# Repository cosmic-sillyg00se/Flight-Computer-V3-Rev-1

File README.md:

# Flight-Computer-V3-Rev-1
(04/2025) Slighty better than my last try, still a total mess tho (also didn't work at all)

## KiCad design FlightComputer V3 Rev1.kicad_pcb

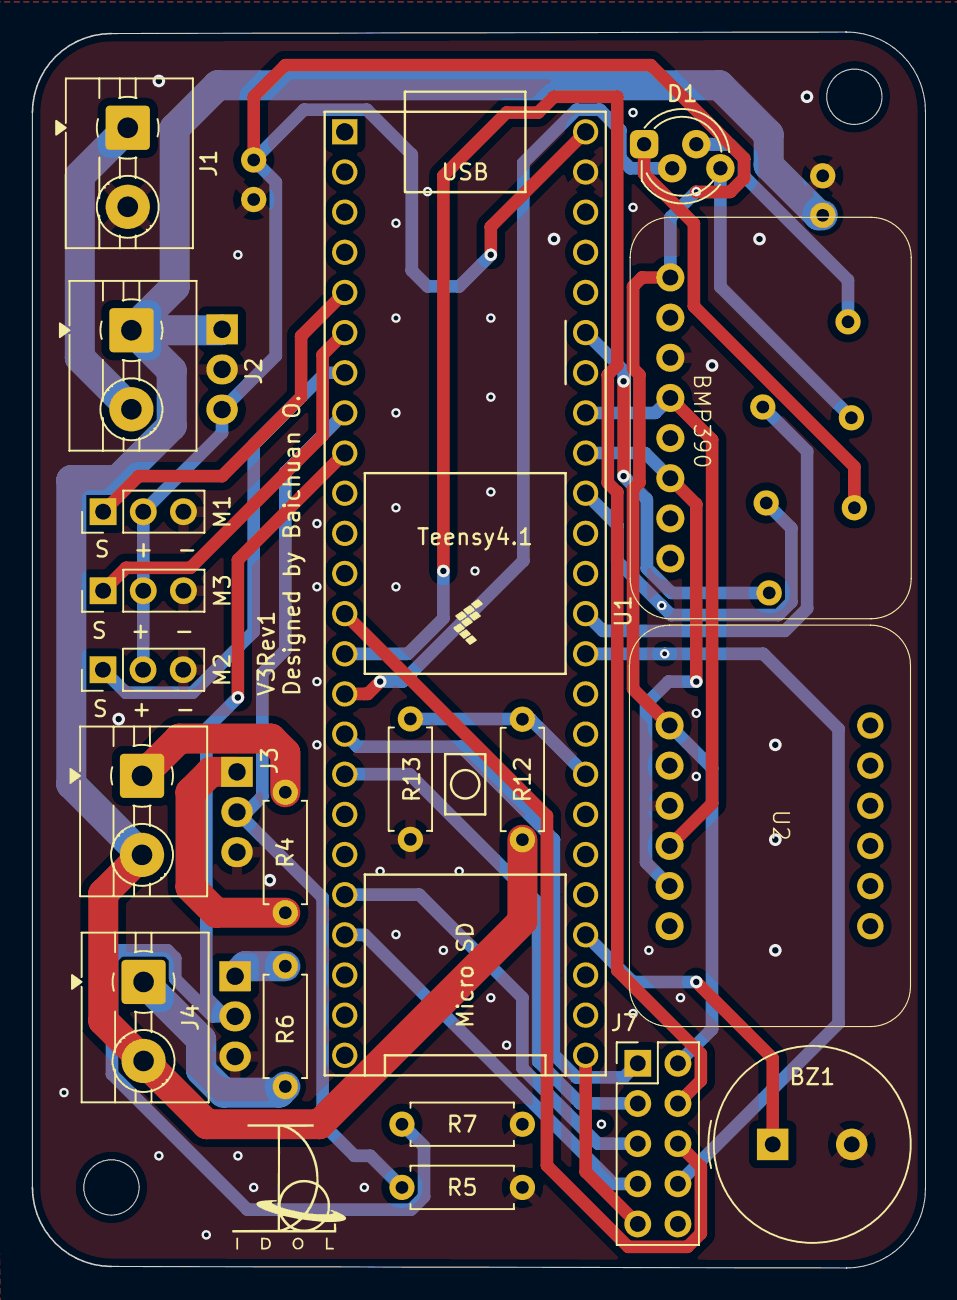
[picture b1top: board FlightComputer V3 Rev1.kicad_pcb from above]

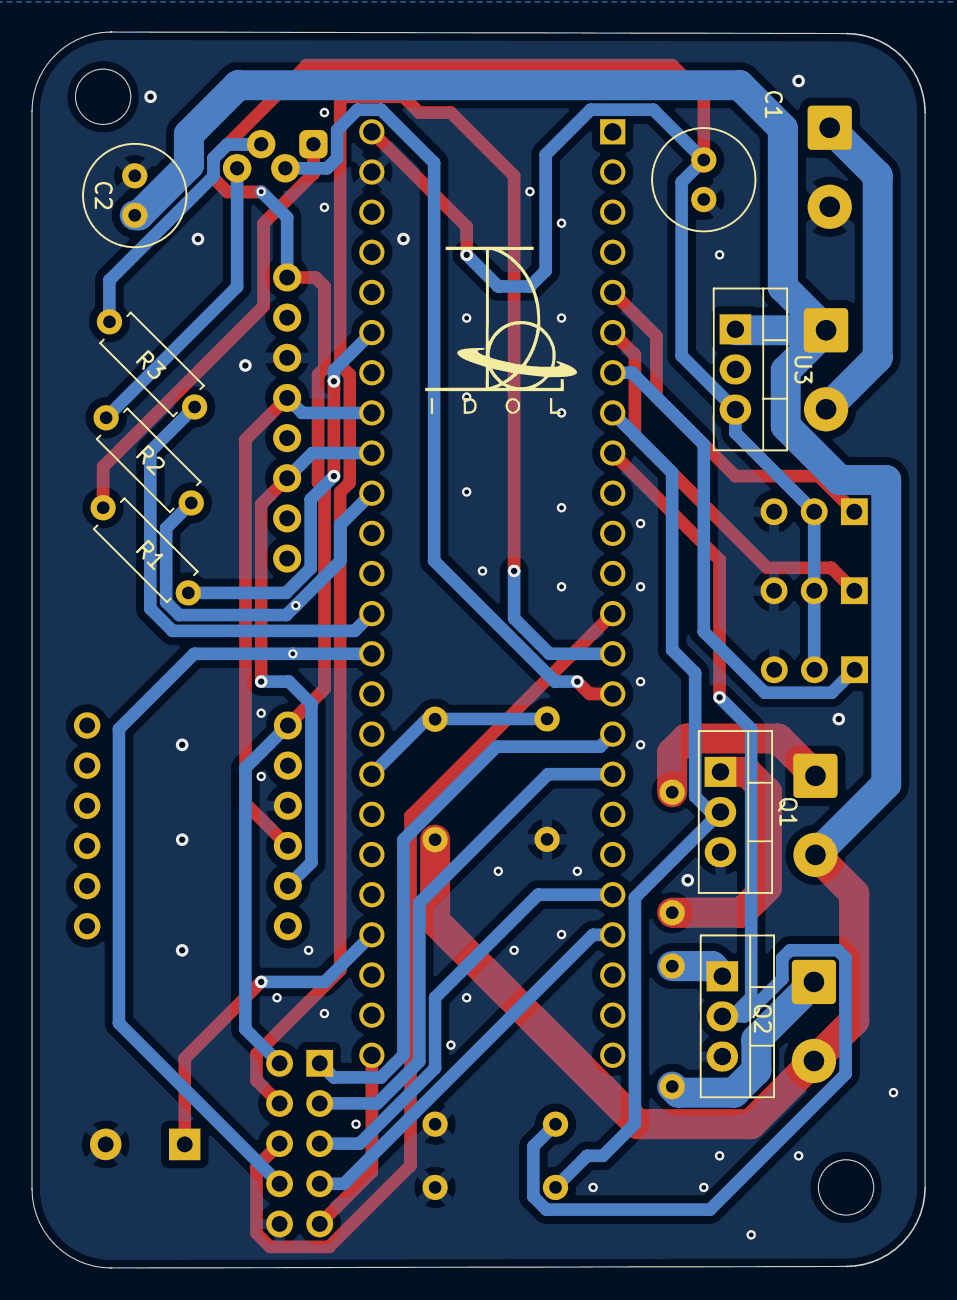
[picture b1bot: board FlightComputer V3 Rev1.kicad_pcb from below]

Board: 2 copper layers, 56.5 x 78.2 mm, 27 parts (8 on the bottom side), 32 nets.

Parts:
BMP390: BMP390
BZ1: Buzzer; Buzzer_TDK_PS1240P02BT_D12.2mm_H6.5mm
C1: 1uF; C_Radial_D6.3mm_H5.0mm_P2.50mm
C2: 10uF; C_Radial_D6.3mm_H5.0mm_P2.50mm
D1: LED_D5.0mm-4_RGB_Staggered_Pins
J1: PWR_IN; TerminalBlock_MaiXu_MX126-5.0-02P_1x02_P5.00mm
J2: SWITCH; TerminalBlock_MaiXu_MX126-5.0-02P_1x02_P5.00mm
J3: PYRO1; TerminalBlock_MaiXu_MX126-5.0-02P_1x02_P5.00mm
J4: PYRO2; TerminalBlock_MaiXu_MX126-5.0-02P_1x02_P5.00mm
J7: PinHeader_2x05_P2.54mm_Vertical
M1, M2, M3: Motor_Servo; PinHeader_1x03_P2.54mm_Vertical
Q1, Q2: NMOS; TO-220-3_Vertical
R1, R2, R3: 40ohm; R_Axial_DIN0207_L6.3mm_D2.5mm_P7.62mm_Horizontal
R4, R6: 1ohm; R_Axial_DIN0207_L6.3mm_D2.5mm_P7.62mm_Horizontal
R5, R7: 1k; R_Axial_DIN0207_L6.3mm_D2.5mm_P7.62mm_Horizontal
R12: 1M; R_Axial_DIN0207_L6.3mm_D2.5mm_P7.62mm_Horizontal
R13: 100K; R_Axial_DIN0207_L6.3mm_D2.5mm_P7.62mm_Horizontal
U1: Teensy4.1; Teensy41
U2: MPU6050
U3: LM7805_TO220; TO-220-3_Vertical

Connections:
+3.3V: D1.2 (A), U1.15 (3V3)
+5V: BMP390.1 (VIN), C1.1, J7.2, M1.2 (+), M2.2 (+), M3.2 (+), U1.48 (VIN), U2.1 (VIN), U3.3 (VO)
+12V: C2.1, J2.1, J3.2, J4.2, R12.2, U3.1 (VI)
+BATT: J1.1, J2.2
/BLU: R2.2, U1.39 (17_A3_TX4_SDA1)
/BUZZER: BZ1.1 (+), U1.28 (36_CS)
/GRN: R3.2, U1.36 (14_A0_TX3_SPDIF_OUT)
/HEADER1: J7.1, U1.16 (24_A10_TX6_SCL2)
/HEADER2: J7.3, U1.17 (25_A11_RX6_SDA2)
/HEADER3: J7.5, U1.20 (28_RX7)
/HEADER4: J7.7, U1.21 (29_TX7)
/HEADER5: J7.9, U1.25 (33_MCLK2)
/MISO: J7.4, U1.14 (12_MISO_MQSL)
/MOSI: J7.6, U1.13 (11_MOSI_CTX1)
/PYRO1: Q1.2 (G), R5.2, U1.8 (6_OUT1D)
/PYRO2: Q2.2 (G), R7.2, U1.9 (7_RX2_OUT1A)
/RED: R1.2, U1.43 (21_A7_RX5_BCLK1)
/SCK: J7.8, U1.35 (13_SCK_LED)
/SCL: BMP390.4 (SCL), U1.41 (19_A5_SCL), U2.4 (SCL)
/SDA: BMP390.6 (SDA), U1.40 (18_A4_SDA), U2.5 (SDA)
/SERVO1: M1.1 (PWM), U1.5 (3_LRCLK2)
/SERVO2: M3.1 (PWM), U1.6 (4_BCLK2)
/SERVO3: M2.1 (PWM), U1.7 (5_IN2)
/VOLTAGE: R12.1, R13.1, U1.32 (40_A16)
GND: BMP390.3 (GND), BZ1.2 (-), C1.2, C2.2, J1.2, J7.10, M1.3 (-), M2.3 (-), M3.3 (-), Q1.3 (S), Q2.3 (S), R5.1, R7.1, R13.2, U1.47 (GND), U2.3 (GND), U3.2 (GND)
unnamed: D1.4 (BLU), R2.1
unnamed: D1.3 (GRN), R3.1
unnamed: D1.1 (RED), R1.1
unnamed: J3.1, R4.2
unnamed: J4.1, R6.2
unnamed: Q1.1 (D), R4.1
unnamed: Q2.1 (D), R6.1

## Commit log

2026-02-05 Added all KiCad Files
